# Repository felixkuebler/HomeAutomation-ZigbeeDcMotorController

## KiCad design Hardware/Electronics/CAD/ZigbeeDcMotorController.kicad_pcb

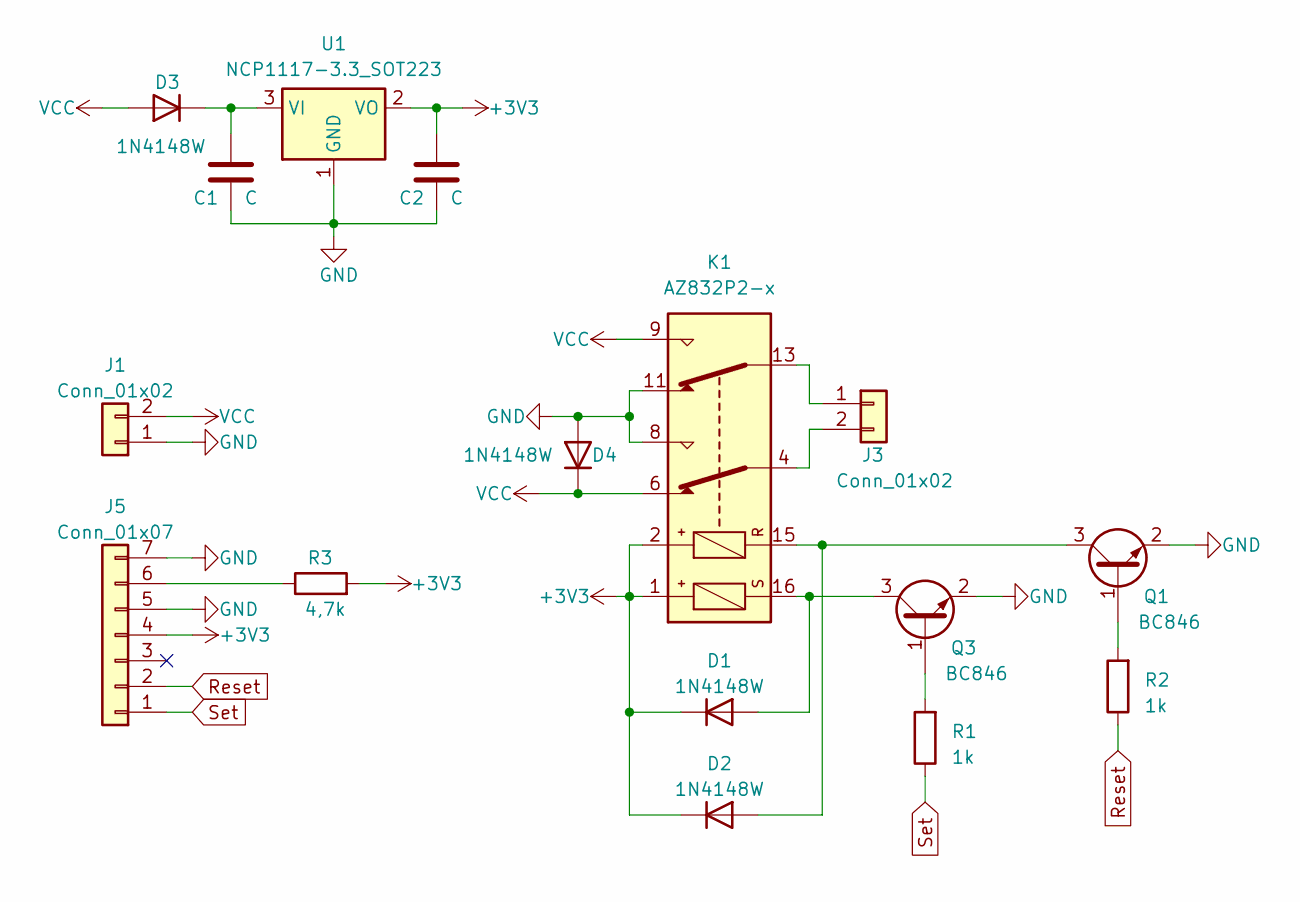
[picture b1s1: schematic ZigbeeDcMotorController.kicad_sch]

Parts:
C1, C2: C; C_0805_2012Metric_Pad1.18x1.45mm_HandSolder
D1, D2, D3, D4: 1N4148W; D_SOD-123
J1, J3: Conn_01x02; TerminalBlock_Phoenix_MKDS-1,5-2-5.08_1x02_P5.08mm_Horizont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
J5: Conn_01x07; ZonoffZigbeePcb
K1: AZ832P2-x; Relay_DPDT_FRT5
Q1, Q3: BC846; SOT-23
R1, R2: 1k; R_0805_2012Metric_Pad1.20x1.40mm_HandSolder
R3: 4,7k; R_0805_2012Metric_Pad1.20x1.40mm_HandSolder
U1: NCP1117-3.3_SOT223; SOT-223-3_TabPin2

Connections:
+3V3: C2.1, D1.1 (K), D2.1 (K), J5.4, K1.1, K1.2, R3.2, U1.2 (VO)
GND: C1.2, C2.2, D4.2 (A), J1.1, J5.5, J5.7, K1.8, K1.11, Q1.2 (E), Q3.2 (E), U1.1 (GND)
unnamed: D1.2 (A), K1.16, Q3.3 (C)
unnamed: D2.2 (A), K1.15, Q1.3 (C)
unnamed: C1.1, D3.1 (K), U1.3 (VI)
unnamed: J3.1, K1.13
unnamed: J3.2, K1.4
unnamed: J5.6, R3.1
unnamed: Q1.1 (B), R2.2
unnamed: Q3.1 (B), R1.2
Reset: J5.2, R2.1
Set: J5.1, R1.1
VCC: D3.2 (A), D4.1 (K), J1.2, K1.6, K1.9

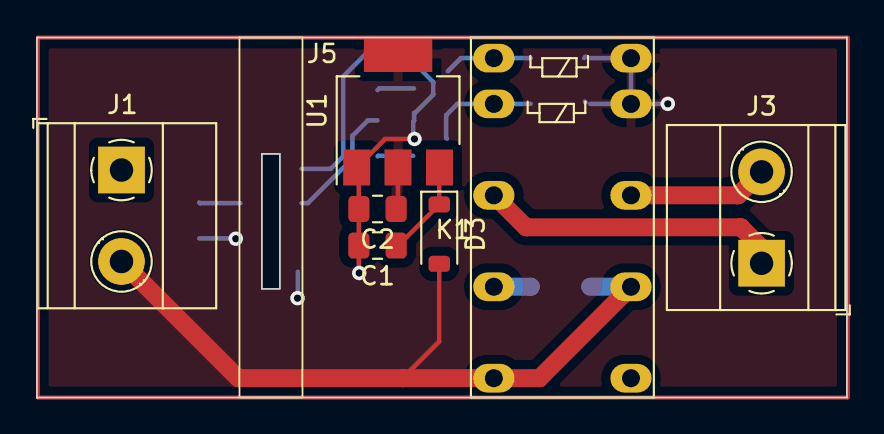
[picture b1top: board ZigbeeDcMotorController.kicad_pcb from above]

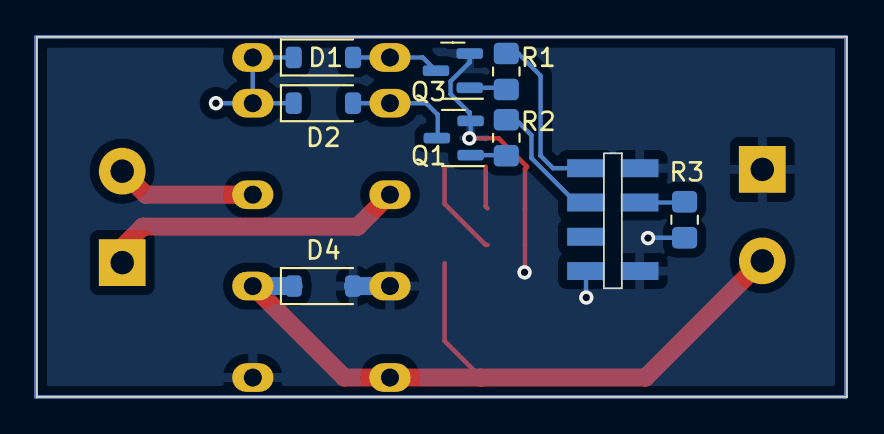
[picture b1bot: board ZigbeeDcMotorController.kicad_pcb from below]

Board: 2 copper layers, 45.0 x 20.0 mm, 16 parts (8 on the bottom side), 13 nets.

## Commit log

2024-02-26 Initial Commit with first design
2024-02-26 Second design with LDO
